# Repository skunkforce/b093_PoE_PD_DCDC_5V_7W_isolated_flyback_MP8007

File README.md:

# edgy_board number b093
This design is part of the [edgy board project](https://github.com/skunkforce/edgy_boards). 

# getting started
This repository uses submodules. After cloning use the command 

```$ git submodule update --init --recursive```

to pull the submodules before opening the project with kicad. 

# Tests
Tests can be found in [TESTS.md](TESTS.md)

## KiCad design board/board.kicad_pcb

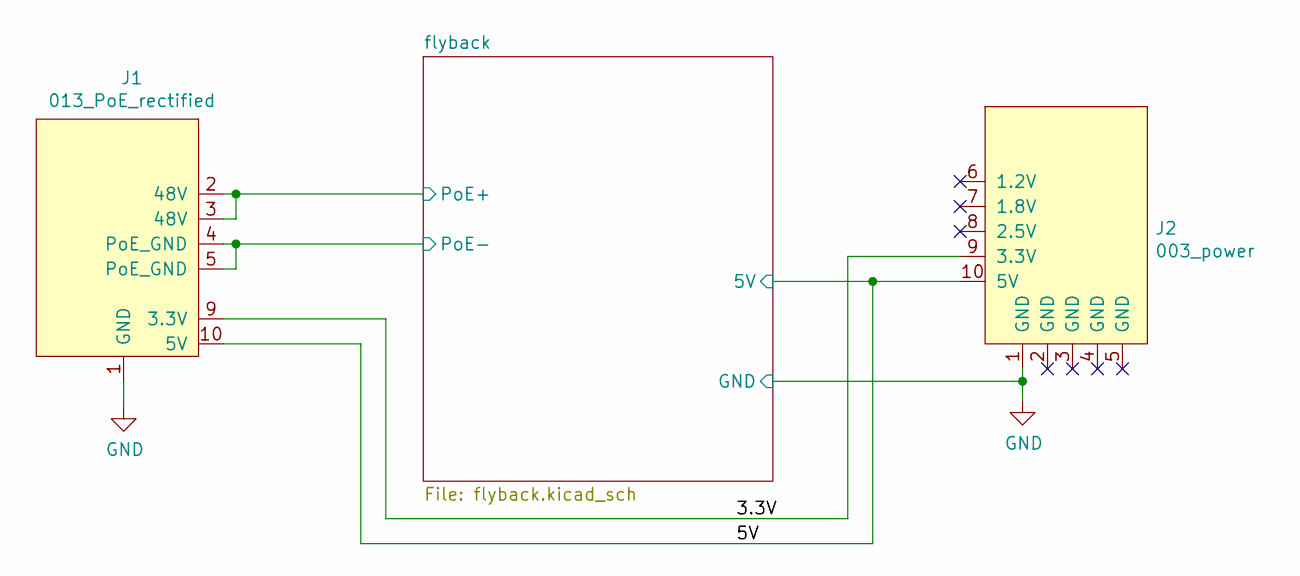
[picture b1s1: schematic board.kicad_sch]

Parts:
J1: 013_PoE_rectified; on_edge_2x05_device
J2: 003_power; on_edge_2x05_host

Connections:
/3.3V: J1.9 (3.3V), J2.9 (3.3V)
/5V: J1.10 (5V), J2.10 (5V); also elsewhere on the board
/flyback/PoE+: J1.2 (48V), J1.3 (48V); also elsewhere on the board
/flyback/PoE-: J1.4 (PoE_GND), J1.5 (PoE_GND); also elsewhere on the board
GND: J1.1 (GND), J2.1 (GND); also elsewhere on the board

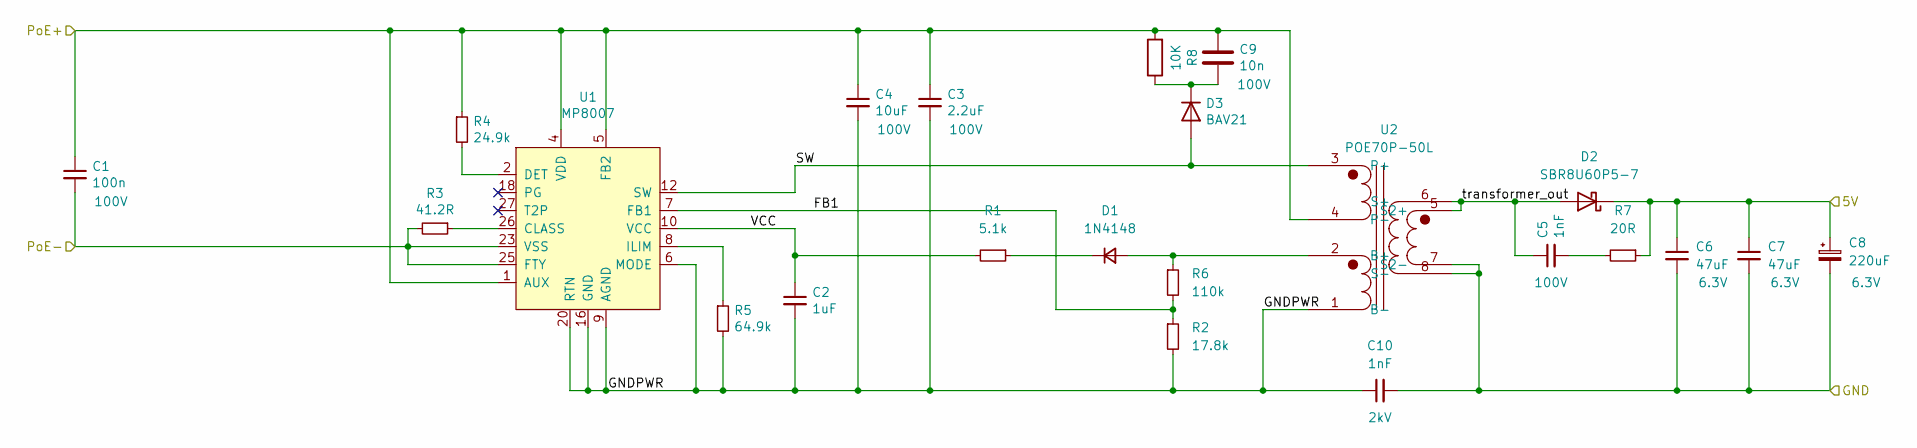
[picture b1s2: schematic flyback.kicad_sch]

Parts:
C1: 100n; C_0603_1608Metric; Voltage 100V
C2: 1uF; C_0603_1608Metric
C3: 2.2uF; C_1210_3225Metric; Voltage 100V
C4: 10uF; C_1210_3225Metric; Voltage 100V
C5: 1nF; C_0603_1608Metric; Voltage 100V; MPN GRM188R72A102KA01D
C6, C7: 47uF; C_1210_3225Metric; Voltage 6.3V
C8: 220uF; CP_Elec_10x10.5; Voltage 6.3V
C9: 10n; C_0805_2012Metric; Voltage 100V; MPN GRM216R72A103KA01D
C10: 1nF; C_1825_4564Metric; Voltage 2kV
D1: 1N4148; D_SOD-323; DigiKey_PN 1N4148WS_R1_00001
D2: SBR8U60P5-7; D_PowerDI-5
D3: BAV21; D_SOD-323_HandSoldering; DigiKey_PN BAV21WS_R1_00001
R1: 5.1k; R_0603_1608Metric
R2: 17.8k; R_0603_1608Metric
R3: 41.2R; R_0603_1608Metric
R4: 24.9k; R_0603_1608Metric
R5: 64.9k; R_0603_1608Metric
R6: 110k; R_0603_1608Metric
R7: 20R; R_0603_1608Metric
R8: 10K; R_1206_3216Metric
U1: MP8007; QFN-28-1EP_4x5mm_P0.5mm_EP2.65x3.65mm_ThermalVias
U2: POE70P-50L; Transformer_Coilcraft_POE70P

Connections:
/5V: C6.1, C7.1, C8.1, D2.1 (K), R7.1; also elsewhere on the board
/flyback/FB1: R2.1, R6.2, U1.7 (FB1)
/flyback/GNDPWR: C2.2, C3.2, C4.2, C10.1, R2.2, R5.2, U1.6 (MODE), U1.9 (AGND), U1.14 (NC), U1.15 (NC), U1.16 (GND), U1.17, U1.19 (NC), U1.20 (RTN), U1.21, U1.22 (NC), U1.29 (GND), U2.1 (B-)
/flyback/PoE+: C1.1, C3.1, C4.1, C9.1, R4.1, R8.2, U1.1 (AUX), U1.4 (VDD), U1.5 (FB2), U2.4 (P-); also elsewhere on the board
/flyback/PoE-: C1.2, R3.2, U1.23 (VSS), U1.24, U1.25 (FTY); also elsewhere on the board
/flyback/SW: D3.2 (A), U1.12 (SW), U1.13, U2.3 (P+)
/flyback/VCC: C2.1, R1.2, U1.10 (VCC)
/flyback/transformer_out: C5.1, D2.2 (A), U2.5 (S2+), U2.6 (S+)
GND: C6.2, C7.2, C8.2, C10.2, U2.7 (S2-), U2.8 (S-); also elsewhere on the board
unnamed: C5.2, R7.2
unnamed: C9.2, D3.1 (K), R8.1
unnamed: D1.1 (K), R1.1
unnamed: D1.2 (A), R6.1, U2.2 (B+)
unnamed: R3.1, U1.26 (CLASS)
unnamed: R4.2, U1.2 (DET)
unnamed: R5.1, U1.8 (ILIM)

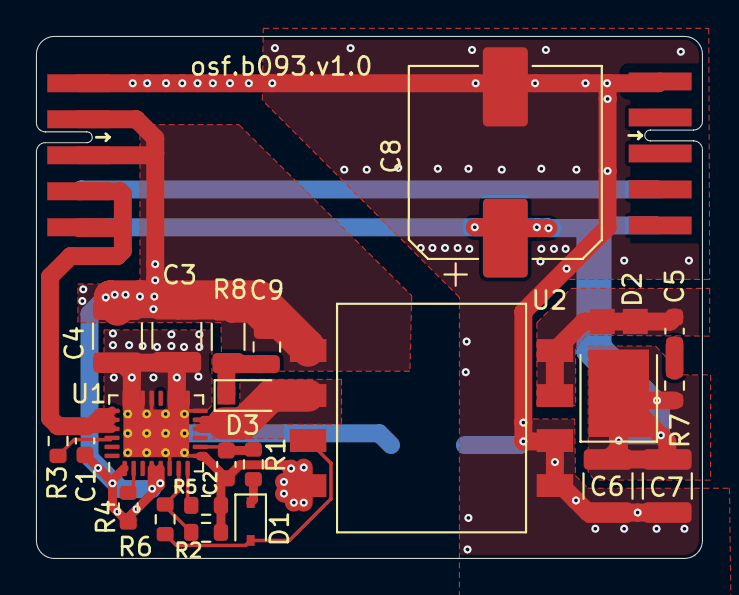
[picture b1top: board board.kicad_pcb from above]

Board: 2 copper layers, 37.0 x 29.0 mm, 25 parts (1 on the bottom side), 17 nets.

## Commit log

2023-03-04 initial
2023-03-19 improved thermal properties of layout
2023-05-29 updated voltage and current setting resistors
